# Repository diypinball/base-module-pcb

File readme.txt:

base-module-r1
==============
Size: Approx. 149mm x 99mm
Layers: 2
Silkscreen: White
Soldermask: Green
Thickness: 1.6mm

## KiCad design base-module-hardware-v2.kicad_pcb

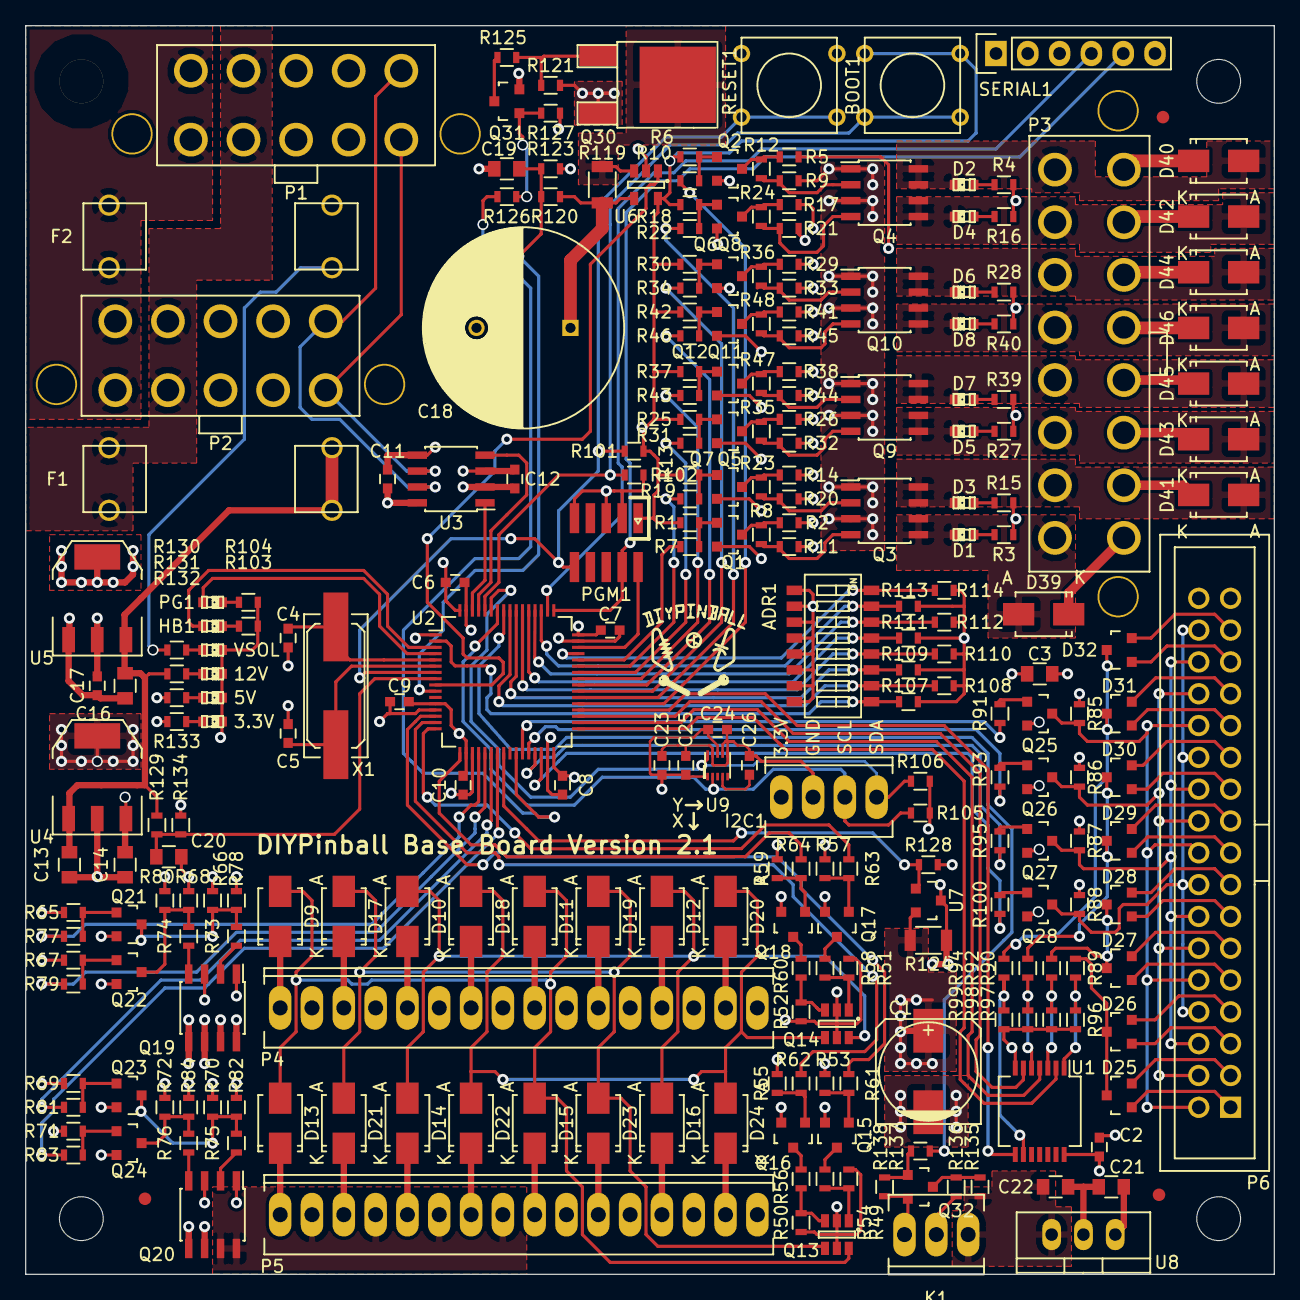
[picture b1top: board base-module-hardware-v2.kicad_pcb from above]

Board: 4 copper layers, 99.7 x 99.7 mm, 263 parts (0 on the bottom side), 197 nets.

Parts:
ADR1: DIPS_08; DIPSWITCH-SMT-08
BOOT1: BUTTON; SW_PUSH_SMALL
C1: 47u; c_elec_8x10
C2, C9, C10, C11, C12, C23, C24, C26: 100n; C_0603
C3, C13, C14, C16, C19, C20, C21, C22: 10u; C_0805
C4, C5: 18p; C_0603
C6, C7, C8: 10n; C_0603
C17: 4.7u; C_0603
C18: 470u; C_Radial_D16_L25_P7.5
C25: 1u; C_0603
D1, D2, D3, D4, D5, D6, D7, D8, D35, D36, D37, D38: LED; LED-0603
D9, D10, D11, D12, D13, D14, D15, D16, D17, D18, D19, D20, D21, D22, D23, D24, D39, D40, D41, D42, D43, D44, D45, D46: S1M; SMA_Standard
D25, D26, D27, D28, D29, D30, D31, D32: BAT54C; SOT-23
F1, F2: FUSE; FC203-20MM
FIDUCIAL: VAL**; FIDUCIAL
FIDUCIAL#2, FIDUCIAL#3: VAL**; FIDUCIAL
HB1: LED; LED-0603
I2C1: CONN_4; Socket_MOLEX-KK-RM2-54mm_Lock_4pin_straight
K1: CONN_3; Socket_MOLEX-KK-RM2-54mm_Lock_3pin_straight
P1, P2: PINBALL-CONNECTOR; PINBALL-CONNECTOR-V
P3: SOLENOID-CONNECTOR; SOLENOID-CONNECTOR-V
P4, P5: CONN_16; Socket_MOLEX-KK-RM2-54mm_Lock_16pin_straight
P6: HE10-34; BOXHEADER-0.100-34
PG1: LED; LED-0603
PGM1: ARM-SWD-HEADER; pin_array_5x2_50mil_smd
Q1, Q2, Q5, Q6, Q7, Q8, Q11, Q12, Q15, Q16, Q17, Q18, Q21, Q22, Q23, Q24, Q25, Q26, Q27, Q28, Q31: BC846; SOT-23
Q3, Q4, Q9, Q10, Q19, Q20: DMN6040SSD; SOIC-8_3.9x4.9mm_Pitch1.27mm
Q13, Q14: DMP2240UDM; SOT-23-6
Q30: FDD5614P; DPAK-2
Q32: BSS138; SOT-23
R1, R6, R8, R9, R13, R18, R20, R21, R25, R30, R32, R33, R37, R42, R44, R45, R49, R50, R51, R52, R53, R55, R57, R59, R65, R67, R69, R71, R78, R80, R82, R84, R85, R86, R87, R88, R89, R90, R92, R94, R96, R97, R98, R99, R101, R102, R107, R108, R109, R110, R111, R112, R113, R114, R121, R127, R138: 10K; R_0603
R2, R5, R7, R10, R14, R17, R19, R22, R26, R29, R31, R34, R38, R41, R43, R46, R54, R56, R58, R60, R61, R62, R63, R64, R66, R68, R70, R72, R77, R79, R81, R83, R91, R93, R95, R100, R103, R104, R126, R132, R133, R135: 1K; R_0603
R3, R4, R15, R16, R27, R28, R39, R40, R131: 2.7K; R_0603
R11, R12, R23, R24, R35, R36, R47, R48, R73, R74, R75, R76, R136, R137: 22; R_0603
R105, R106: 4.7K; R_0603
R119: .003; R_1206
R120: 95.3K 1%; R_0603
R123, R128, R134: 5.1K 1%; R_0603
R124: 0.075; R_1206
R125, R130: 27K; R_0603
R129: 20.5K 1%; R_0603
RESET1: BUTTON; SW_PUSH_SMALL
SERIAL1: FTDI_SERIAL; Socket_Strip_Straight_1x06
U1: 74LVC14; SSOP-14_5.3x6.2mm_Pitch0.65mm
U2: STM32F072R; LQFP-64_10x10mm_Pitch0.5mm
U3: MCP2562; SOIC-8_3.9x4.9mm_Pitch1.27mm
U4: MC78L05; SOT-223
U5: AP1117IE33G; SOT-223
U6: ZXCT1086E5TA; SOT-23-5
U7: ZXCT1107SA-7; SOT-23
U8: LM7805CT; TO-220_Neutral123_Vertical
U9: MMA8653FC; DFN-10
X1: 8.000 MHz; Q_49U3HMS

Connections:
+3.3V: ADR1.1, ADR1.2, ADR1.3, ADR1.4, ADR1.5, ADR1.6, ADR1.7, ADR1.8, BOOT1.2, C2.1, C6.1, C7.1, C8.1, C9.1, C10.1, C11.1, C17.1, C23.1, C24.1, C25.1, I2C1.1, PGM1.1, R1.1, R6.1, R13.1, R18.1, R25.1, R30.1, R37.1, R42.1, R65.1, R67.1, R69.1, R71.1, R101.1, R105.1, R106.1, R133.1, U1.14, U2.1, U2.13, U2.19, U2.32, U2.48, U2.64, U3.5, U5.2, U5.4, U6.5, U9.1, U9.8
+5V: C12.1, C14.1, R132.1, U3.3, U4.3
+12V: C3.1, C13.1, C16.1, C21.1, F1.2, P6.34, R2.1, R3.1, R4.1, R5.1, R14.1, R15.1, R16.1, R17.1, R26.1, R27.1, R28.1, R29.1, R38.1, R39.1, R40.1, R41.1, R85.1, R86.1, R87.1, R88.1, R124.2, R129.2, R131.1, U4.1, U5.3, U7.3, U8.1
/Accelerometer/SCL: I2C1.3, R105.2, U2.58, U9.2
/Accelerometer/SDA: I2C1.4, R106.2, U2.59, U9.10
/Control Logic/12V_SENSE: C20.1, R129.1, R134.1, U2.8
/Control Logic/ADDRESS0: ADR1.16, R114.1, U2.45
/Control Logic/ADDRESS1: ADR1.15, R113.1, U2.51
/Control Logic/ADDRESS2: ADR1.14, R112.1, U2.52
/Control Logic/ADDRESS3: ADR1.13, R111.1, U2.53
/Control Logic/ADDRESS4: ADR1.12, R110.1, U2.54
/Control Logic/ADDRESS5: ADR1.11, R109.1, U2.55
/Control Logic/ADDRESS6: ADR1.10, R108.1, U2.56
/Control Logic/ADDRESS7: ADR1.9, R107.1, U2.2
/Control Logic/BOOTLOADER: BOOT1.1, R102.1, U2.60
/Control Logic/CANH: P1.5, P2.5, U3.7
/Control Logic/CANL: P1.10, P2.10, U3.6
/Control Logic/CANRX: U2.61, U3.4
/Control Logic/CANTX: U2.62, U3.1
/Control Logic/HEARTBEAT: HB1.2, U2.3
/Control Logic/LAMP_COL0: R77.1, U2.20
/Control Logic/LAMP_COL1: R79.1, U2.21
/Control Logic/LAMP_COL2: R81.1, U2.22
/Control Logic/LAMP_COL3: R83.1, U2.23
/Control Logic/LAMP_ROW0: R61.1, U2.14
/Control Logic/LAMP_ROW1: R62.1, U2.15
/Control Logic/LAMP_ROW2: R63.1, U2.16
/Control Logic/LAMP_ROW3: R64.1, U2.17
/Control Logic/POWER_GOOD: PG1.2, U2.4
/Control Logic/RXD: SERIAL1.4, U2.50
/Control Logic/SOLENOID0: R7.1, U2.44
/Control Logic/SOLENOID1: R19.1, U2.43
/Control Logic/SOLENOID2: R31.1, U2.42
/Control Logic/SOLENOID3: R43.1, U2.41
/Control Logic/SOLENOID4: R46.1, U2.40
/Control Logic/SOLENOID5: R34.1, U2.39
/Control Logic/SOLENOID6: R22.1, U2.38
/Control Logic/SOLENOID7: R10.1, U2.37
/Control Logic/SWCLK: PGM1.4, SERIAL1.5, U2.49
/Control Logic/SWDIO: PGM1.2, U2.46
/Control Logic/VSOL_PRECHARGE_PWM: R126.2, U2.26
/Control Logic/VSOL_SENSE: C19.1, R120.2, R123.1, U2.10
/Control Logic/~RESET: PGM1.10, R101.2, RESET1.2, U2.7
/Lamp Driver/LAMP_12V: C1.1, Q13.2, Q13.5, Q14.2, Q14.5, R49.1, R50.1, R51.1, R52.1, R66.1, R68.1, R70.1, R72.1, R124.1, U7.2
/Power Supply/12V_IN: F1.1, P1.2, P1.7, P2.2, P2.7
/Power Supply/ILAMP_SENSE_OUT: R128.1, U2.24, U7.1
/Power Supply/ISOL_SENSE_OUT: U2.9, U6.1
/Power Supply/VSOL_IN: F2.1, P1.1, P1.6, P2.1, P2.6
/RGB LED Output/RGB_DATA: R137.2, U2.57
/Solenoid Driver/SOL_PWR: C18.1, D39.1, D40.1, D41.1, D42.1, D43.1, D44.1, D45.1, D46.1, P3.9, P3.10, P3.11, P3.12, P3.13, P3.14, P3.15, P3.16, R119.1, R120.1, U6.4
/Switch Matrix/COL0: R91.2, U2.27
/Switch Matrix/COL0_SWITCHED: P6.2, P6.10, P6.18, P6.26, Q25.3, R85.2
/Switch Matrix/COL1: R93.2, U2.28
/Switch Matrix/COL1_SWITCHED: P6.4, P6.12, P6.20, P6.28, Q26.3, R86.2
/Switch Matrix/COL2: R95.2, U2.29
/Switch Matrix/COL2_SWITCHED: P6.6, P6.14, P6.22, P6.30, Q27.3, R87.2
/Switch Matrix/COL3: R100.2, U2.30
/Switch Matrix/COL3_SWITCHED: P6.8, P6.16, P6.24, P6.32, Q28.3, R88.2
/Switch Matrix/ROW0: U1.2, U2.33
/Switch Matrix/ROW0_SWITCHED: D25.3, D26.3, R89.2
/Switch Matrix/ROW1: U1.4, U2.34
/Switch Matrix/ROW1_SWITCHED: D27.3, D28.3, R90.2
/Switch Matrix/ROW2: U1.6, U2.35
/Switch Matrix/ROW2_SWITCHED: D29.3, D30.3, R92.2
/Switch Matrix/ROW3: U1.8, U2.36
/Switch Matrix/ROW3_SWITCHED: D31.3, D32.3, R94.2
GND: C1.2, C2.2, C3.2, C4.2, C5.2, C6.2, C7.2, C8.2, C9.2, C10.2, C11.2, C12.2, C13.2, C14.2, C16.2, C17.2, C18.2, C19.2, C20.2, C21.2, C22.2, C23.2, C24.2, C25.2, C26.2, D35.1, D36.1, D37.1, D38.1, I2C1.2, K1.3, P1.3, P1.4, P1.8, P1.9, P2.3, P2.4, P2.8, P2.9, P6.33, PGM1.3, PGM1.5, PGM1.9, Q1.2, Q2.2, Q3.1, Q3.3, Q4.1, Q4.3, Q5.2, Q6.2, Q7.2, Q8.2, Q9.1, Q9.3, Q10.1, Q10.3, Q11.2, Q12.2, Q15.2, Q16.2, Q17.2, Q18.2, Q19.1, Q19.3, Q20.1, Q20.3, Q21.2, Q22.2, Q23.2, Q24.2, Q25.2, Q26.2, Q27.2, Q28.2, Q31.2, Q32.2, R8.1, R9.1, R20.1, R21.1, R32.1, R33.1, R44.1, R45.1, R53.1, R55.1, R57.1, R59.1, R78.2, R80.2, R82.2, R84.2, R96.2, R97.2, R98.2, R99.2, R102.2, R103.2, R104.2, R107.2, R108.2, R109.2, R110.2, R111.2, R112.2, R113.2, R114.2, R123.2, R127.2, R128.2, R134.2, R138.2, RESET1.1, SERIAL1.1, U1.7, U2.12, U2.18, U2.31, U2.47, U2.63, U3.2, U3.8, U4.2, U4.4, U5.1, U6.2, U8.2, U9.6, U9.7, U9.9
unnamed: C4.1, U2.5, X1.1
unnamed: C5.1, U2.6, X1.2
unnamed: C22.1, K1.1, R135.1, U8.3
unnamed: C26.1, U9.4
unnamed: D1.1, D39.2, P3.1, Q3.5, Q3.6
unnamed: D1.2, R3.2
unnamed: D2.1, D40.2, P3.8, Q4.7, Q4.8
unnamed: D2.2, R4.2
unnamed: D3.1, D41.2, P3.2, Q3.7, Q3.8
unnamed: D3.2, R15.2
unnamed: D4.1, D42.2, P3.7, Q4.5, Q4.6
unnamed: D4.2, R16.2
unnamed: D5.2, R27.2
unnamed: D6.2, R28.2
unnamed: D7.2, R39.2
unnamed: D8.2, R40.2
unnamed: D9.1, P4.1
unnamed: D10.1, P4.5
unnamed: D10.2, D12.2, D14.2, D16.2, Q14.6
unnamed: D11.1, P4.9
unnamed: D9.2, D11.2, D13.2, D15.2, Q13.6
unnamed: D12.1, P4.13
unnamed: D13.1, P5.1
unnamed: D14.1, P5.5
unnamed: D15.1, P5.9
unnamed: D16.1, P5.13
unnamed: D17.1, P4.3
unnamed: D17.2, D19.2, D21.2, D23.2, Q13.4
unnamed: D18.1, P4.7
unnamed: D18.2, D20.2, D22.2, D24.2, Q14.4
unnamed: D19.1, P4.11
unnamed: D20.1, P4.15
unnamed: D21.1, P5.3
unnamed: D22.1, P5.7
unnamed: D23.1, P5.11
unnamed: D24.1, P5.15
unnamed: D25.1, P6.1
unnamed: D25.2, P6.3
unnamed: D26.1, P6.5
unnamed: D26.2, P6.7
unnamed: D27.1, P6.9
unnamed: D27.2, P6.11
unnamed: D28.1, P6.13
unnamed: D28.2, P6.15
unnamed: D29.1, P6.17
unnamed: D29.2, P6.19
unnamed: D30.1, P6.21
unnamed: D30.2, P6.23
unnamed: D31.1, P6.25
unnamed: D31.2, P6.27
unnamed: D32.1, P6.29
unnamed: D32.2, P6.31
unnamed: D35.2, R130.2
unnamed: D36.2, R131.2
unnamed: D37.2, R132.2
unnamed: D38.2, R133.2
unnamed: D5.1, D43.2, P3.3, Q9.5, Q9.6
unnamed: D6.1, D44.2, P3.6, Q10.7, Q10.8
unnamed: D7.1, D45.2, P3.4, Q9.7, Q9.8
unnamed: D8.1, D46.2, P3.5, Q10.5, Q10.6
unnamed: HB1.1, R103.1
unnamed: K1.2, R136.1
unnamed: P4.2, P4.4, P4.6, P4.8, Q19.7, Q19.8
unnamed: P4.10, P4.12, P4.14, P4.16, Q19.5, Q19.6
unnamed: P5.2, P5.4, P5.6, P5.8, Q20.7, Q20.8
unnamed: P5.10, P5.12, P5.14, P5.16, Q20.5, Q20.6
unnamed: PG1.1, R104.1
unnamed: Q1.1, R1.2, R7.2
unnamed: Q1.3, R2.2, R11.2
unnamed: Q2.1, R6.2, R10.2
unnamed: Q2.3, R5.2, R12.1
unnamed: Q3.2, R20.2, R23.1
unnamed: Q3.4, R8.2, R11.1
unnamed: Q4.2, R9.2, R12.2
unnamed: Q4.4, R21.2, R24.2
unnamed: Q5.1, R13.2, R19.2
unnamed: Q5.3, R14.2, R23.2
unnamed: Q6.1, R18.2, R22.2
unnamed: Q6.3, R17.2, R24.1
unnamed: Q7.1, R25.2, R31.2
unnamed: Q7.3, R26.2, R35.2
unnamed: Q8.1, R30.2, R34.2
unnamed: Q8.3, R29.2, R36.1
unnamed: Q9.2, R44.2, R47.1
unnamed: Q9.4, R32.2, R35.1
unnamed: Q10.2, R33.2, R36.2
unnamed: Q10.4, R45.2, R48.2
unnamed: Q11.1, R37.2, R43.2
unnamed: Q11.3, R38.2, R47.2
unnamed: Q12.1, R42.2, R46.2
unnamed: Q12.3, R41.2, R48.1
unnamed: Q13.1, R49.2, R54.1
unnamed: Q13.3, R50.2, R56.1
unnamed: Q14.1, R51.2, R58.1
unnamed: Q14.3, R52.2, R60.1
unnamed: Q15.1, R53.2, R61.2
unnamed: Q15.3, R54.2
unnamed: Q16.1, R55.2, R62.2
unnamed: Q16.3, R56.2
unnamed: Q17.1, R57.2, R63.2
unnamed: Q17.3, R58.2
unnamed: Q18.1, R59.2, R64.2
unnamed: Q18.3, R60.2
unnamed: Q19.2, R73.1
unnamed: Q19.4, R74.2
unnamed: Q20.2, R75.2
unnamed: Q20.4, R76.2
unnamed: Q21.1, R65.2, R77.2
unnamed: Q21.3, R66.2, R73.2, R78.1
unnamed: Q22.1, R67.2, R79.2
unnamed: Q22.3, R68.2, R74.1, R80.1
unnamed: Q23.1, R69.2, R81.2
unnamed: Q23.3, R70.2, R75.1, R82.1
unnamed: Q24.1, R71.2, R83.2
unnamed: Q24.3, R72.2, R76.1, R84.1
unnamed: Q25.1, R91.1
unnamed: Q26.1, R93.1
unnamed: Q27.1, R95.1
unnamed: Q28.1, R100.1
unnamed: Q30.D, R119.2, U6.3
unnamed: Q30.G, R121.2, R125.1
unnamed: Q31.1, R126.1, R127.1
unnamed: Q31.3, R125.2
unnamed: Q32.1, R137.1, R138.1
unnamed: Q32.3, R135.2, R136.2
unnamed: R89.1, R96.1, U1.1
unnamed: R90.1, R97.1, U1.3
unnamed: R92.1, R98.1, U1.5
unnamed: R94.1, R99.1, U1.9
VEE: F2.2, Q30.S, R121.1, R130.1

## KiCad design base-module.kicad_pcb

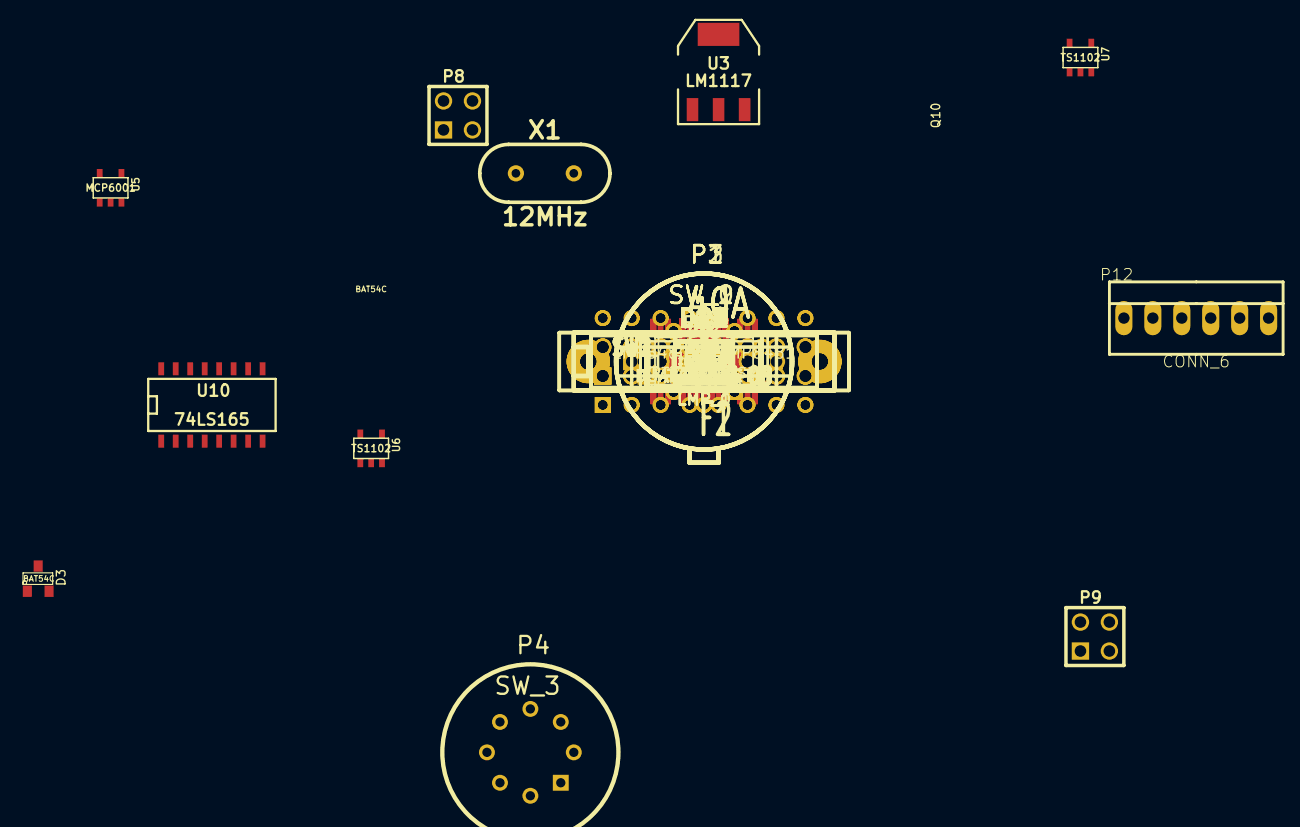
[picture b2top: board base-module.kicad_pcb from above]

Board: 2 copper layers, 203 parts (0 on the bottom side), 137 nets, no tracks yet.

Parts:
3V1, 5V1, 12V1: LED; LED-0805
C1, C2, C3, C4: CYA; SM0805
C5: 100n; SM0805
C6: 10uF; SM1206POL
C7, C8, C10, C14, C15, C20: 100nF; SM0805
C9: 3.3nF; SM0805
C11: DNP; SM0805
C12: 22uF; SM0805
C13: 22nF; SM0805
C16, C17: 0.047uF; SM0805
C18, C27: 100nf; SM0805
C19, C22, C23, C26: C; SM0805
C21, C25: 10nF; SM0805
C24: 1nF; SM0805
D1, D2, D3, D4, D5, D6, D7, D8: BAT54C; SOT23
D9, D10, D11, D12: ZENERSMALL; SOT23
D13, D14, D17, D18, D21, D22, D25, D26: DIODE; Diode-SMA_Handsoldering_RevA_27July2010
D15, D16, D19, D20, D23, D24, D27, D28: LED; LED-0805
D29: DNP; Diode-SMA_Handsoldering_RevA_27July2010
D30, D31: ZENER; SOT23
DBG1: LED; LED-0805
F1, F2: 40A; FUSE5-20
HB1: LED; LED-0805
L1: 15uH; SM2512
P1: SW_0; H08
P2: SW_2; H08
P3: SW_1; H08
P4: SW_3; H08
P5: LMP_0; pin_array_8x2
P6: LMP_1; pin_array_8x2
P7, P8, P9, P10: CONN_2X2; PIN_ARRAY_2X2
P11: CONN_5; PIN_ARRAY-6X1
P12: CONN_6; PINHEAD1-6
P13: CONN_4; PIN_ARRAY_4x1
P14: JTAG; PIN_ARRAY_5x2
PWR1: LED; LED-0805
Q1, Q2, Q3, Q4, Q5, Q6, Q7, Q8, Q9, Q10, Q11, Q12, Q17, Q18, Q19, Q20, Q21, Q22, Q23, Q24: NPN; SOT23
Q13, Q15: DUAL_MOSFET_P; SO8N
Q14, Q16, Q25, Q26, Q27, Q28: DUAL_MOSFET_N; SO8N
R1, R2, R3, R4, R5, R6, R7, R8, R9, R10, R11, R12, R13, R14, R15, R16, R17, R18, R19, R20, R21, R22, R23, R24, R25, R26, R27, R28, R29, R30, R31, R32, R33, R34, R35, R36, R37, R38, R39, R40, R41, R42, R43, R44, R49, R52, R53, R54, R55, R60, R61, R62, R63, R64, R65, R66: R; SM0805
R45: 100k; SM0805
R46: 20k; SM0805
R47: 62k; SM0805
R48: 11.8k; SM0805
R50: 680; SM0805
R51: 1K; SM0805
R56: 0; SM0805
R57: DNP; SM0805
R58, R59: 60; SM0805
RP1, RP2, RP3, RP4, RP5, RP6, RP7, RP8, RP9, RP10, RP11, RP12, RP13: R_PACK4; SM0805
RP14, RP15: R_PACK8; SM0805
SW1, SW2: DIPS_08; DIP-16__300
U1: 74HC14; SO14E
U2: RT7247AHGSP; SO8E
U3: LM1117; SOT223
U4: LMP8480_/_LMP8481; MSOP_8
U5: MCP6001; SOT23-5
U6, U7: TS1102; SOT23-5
U9: 74LS595; SO16N
U10, U11: 74LS165; SO16N
X1: 12MHz; HC-49V

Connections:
+3.3V: C5.1, C13.1, C18.1, C20.1, C21.1, C25.1, P13.1, R44.1, R57.1, R60.1, R63.1, R64.1, R65.1, SW1.1, SW1.2, SW1.3, SW1.4, SW1.5, SW1.6, SW1.7, SW1.8, SW2.1, SW2.2, SW2.3, SW2.4, SW2.5, SW2.6, SW2.7, SW2.8, U1.14, U3.2, U9.10, U9.16, U10.16, U11.16
+5V: C12.1, C14.1, C15.1, C27.1, D29.1, L1.2, R43.1, R47.1, U3.3, U4.2, U5.5
+12V: C6.1, F2.2, R42.1, R45.1, R52.1, R53.1, R61.1, U2.2, U6.5, U7.5
/3V3CurrentSense/SENSE_OUT: C16.1, U6.3
/Controller/12V_SENSE_VOLTAGE: C26.1, D31.2, R61.2, R62.1
/Controller/CANH: P11.3, R58.1
/Controller/CANL: P11.4, R59.2
/Controller/DIP_CLOCK: U10.2, U11.2
/Controller/DIP_LOAD: U10.1, U11.1
/Controller/HB_LED: DBG1.2, R66.1
/Controller/I2C_C: P13.3, R64.2
/Controller/I2C_D: P13.4, R63.2
/Controller/JTAG_RESET: P14.10, R60.2
/Controller/LMP_CURRENT: C17.1, U7.3
/Controller/LMP_ROW_0: RP8.1, U9.15
/Controller/LMP_ROW_1: RP8.2, U9.1
/Controller/SOL_PWR_SENSE_VOLTAGE: C19.1, D30.2, R54.2, R55.1
/CurrentSense/PWR_OUT: D13.2, D14.2, D17.2, D18.2, D21.2, D22.2, D25.2, D26.2, P7.2, P7.4, P8.2, P8.4, P9.2, P9.4, P10.2, P10.4, R17.1, R19.1, R21.1, R23.1, R25.1, R27.1, R29.1, R31.1, R33.1, R34.1, R35.1, R36.1, R37.1, R38.1, R39.1, R40.1, R49.2, U4.8
/CurrentSense/SNS_OUT: R50.1, U5.1
/LampMatrix/COL0: RP7.1, RP9.1, U9.4
/LampMatrix/COL1: RP7.2, RP9.2, U9.5
/LampMatrix/LMP_0M: P5.2, P5.10, P6.2, P6.10
/LampMatrix/LMP_0P: P5.1, P5.3, P5.5, P5.7
/LampMatrix/LMP_1M: P5.4, P5.12, P6.4, P6.12
/LampMatrix/LMP_1P: P5.9, P5.11, P5.13, P5.15
/LampMatrix/LMP_2M: P5.6, P5.14, P6.6, P6.14
/LampMatrix/LMP_2P: P6.1, P6.3, P6.5, P6.7
/LampMatrix/LMP_3M: P5.8, P5.16, P6.8, P6.16
/LampMatrix/LMP_3P: P6.9, P6.11, P6.13, P6.15
/LampMatrix/LMP_PWR: R1.1, R3.1, R5.1, R7.1, R9.1, R11.1, R13.1, R15.1, R53.2, U7.4
/PowerSupply/12V: F2.1, P11.2
/PowerSupply/50V: F1.1, P11.1
/PowerSupply/Power_EN: C7.1, R45.2, U2.7
/SolenoidDriver/SOLENOID0: RP10.1, RP12.1
/SolenoidDriver/SOLENOID1: RP10.2, RP12.2
/SolenoidDriver/SOLENOID4: RP11.1, RP13.1
/SolenoidDriver/SOLENOID5: RP11.2, RP13.2
/SwitchMatrix/12V_IN: R52.2, RP1.1, RP1.2, U6.4
/SwitchMatrix/COL0: RP2.1, RP3.1
/SwitchMatrix/COL0_POWERED: P1.1, P2.1, P3.1, P4.1, Q1.3
/SwitchMatrix/COL1: RP2.2, RP3.2
/SwitchMatrix/COL1_POWERED: P1.3, P2.3, P3.3, P4.3, Q2.3
/SwitchMatrix/COL2_POWERED: P1.5, P2.5, P3.5, P4.5, Q3.3
/SwitchMatrix/COL3_POWERED: P1.7, P2.7, P3.7, P4.7, Q4.3
/SwitchMatrix/ROW0_MATRIX: D1.3, D2.3, RP5.1
/SwitchMatrix/ROW1_MATRIX: D5.3, D6.3, RP5.2
/SwitchMatrix/ROW2_MATRIX: D3.3, D4.3
/SwitchMatrix/ROW3_MATRIX: D7.3, D8.3
GND: 3V1.2, 5V1.2, 12V1.2, C1.2, C2.2, C3.2, C4.2, C5.2, C6.2, C7.2, C8.2, C11.2, C12.2, C13.2, C14.2, C15.2, C16.2, C17.2, C18.2, C19.2, C20.2, C21.2, C22.2, C23.2, C24.2, C25.2, C26.2, C27.2, D9.1, D10.1, D11.1, D12.1, D30.1, D31.1, HB1.2, P11.5, P12.1, P13.2, P14.3, P14.5, P14.9, PWR1.2, Q1.1, Q2.1, Q3.1, Q4.1, Q5.1, Q6.1, Q7.1, Q8.1, Q9.1, Q10.1, Q11.1, Q12.1, Q17.1, Q18.1, Q19.1, Q20.1, Q21.1, Q22.1, Q23.1, Q24.1, R2.2, R4.2, R6.2, R8.2, R10.2, R12.2, R14.2, R16.2, R18.2, R20.2, R22.2, R24.2, R26.2, R28.2, R30.2, R32.2, R46.2, R48.2, R51.2, R55.2, R56.1, R62.2, RP4.1, RP4.2, RP6.1, RP6.2, RP14.1, RP14.2, RP15.1, RP15.2, U1.7, U2.4, U3.1, U4.4, U5.2, U6.1, U6.2, U7.1, U7.2, U9.8, U9.13, U10.8, U10.10, U10.15, U11.8, U11.15
unnamed: D6.2, P3.8
unnamed: D6.1, P3.6
unnamed: D5.1, P3.4
unnamed: D5.2, P3.2
unnamed: D1.2, P1.2
unnamed: D2.2, P1.8
unnamed: D1.1, P1.4
unnamed: D2.1, P1.6
unnamed: D8.1, P4.6
unnamed: D8.2, P4.8
unnamed: D7.1, P4.4
unnamed: D7.2, P4.2
unnamed: D3.2, P2.2
unnamed: D3.1, P2.4
unnamed: D4.1, P2.6
unnamed: D4.2, P2.8
unnamed: C1.1, D9.3, U1.1
unnamed: C4.1, D12.3, U1.9
unnamed: C3.1, D11.3, U1.5
unnamed: C2.1, D10.3, U1.3
unnamed: Q11.3, R13.2, R14.1
unnamed: Q5.3, R1.2, R2.1
unnamed: Q9.3, R9.2, R10.1
unnamed: Q7.3, R5.2, R6.1
unnamed: Q6.3, R3.2, R4.1
unnamed: Q12.3, R15.2, R16.1
unnamed: Q10.3, R11.2, R12.1
unnamed: Q8.3, R7.2, R8.1
unnamed: D14.1, D16.2, P8.1
unnamed: Q20.3, R23.2, R24.1
unnamed: Q18.3, R19.2, R20.1
unnamed: Q24.3, R31.2, R32.1
unnamed: Q22.3, R27.2, R28.1
unnamed: D20.1, R36.2
unnamed: D24.1, R38.2
unnamed: D28.1, R40.2
unnamed: D26.1, D28.2, P10.3
unnamed: D22.1, D24.2, P10.1
unnamed: D18.1, D20.2, P8.3
unnamed: D16.1, R34.2
unnamed: D15.1, R33.2
unnamed: D19.1, R35.2
unnamed: D23.1, R37.2
unnamed: D27.1, R39.2
unnamed: D25.1, D27.2, P9.3
unnamed: D21.1, D23.2, P9.1
unnamed: D17.1, D19.2, P7.3
unnamed: D13.1, D15.2, P7.1
unnamed: Q19.3, R21.2, R22.1
unnamed: Q21.3, R25.2, R26.1
unnamed: Q17.3, R17.2, R18.1
unnamed: Q23.3, R29.2, R30.1
unnamed: C10.1, D29.2, U2.1
unnamed: 5V1.1, R43.2
unnamed: 3V1.1, R44.2
unnamed: PWR1.1, R41.2
unnamed: 12V1.1, R42.2
unnamed: R47.2, R48.1, U2.5
unnamed: C8.1, U2.8
unnamed: C10.2, L1.1, U2.3
unnamed: C9.2, R46.1
unnamed: C9.1, C11.1, U2.6
unnamed: DBG1.1, R65.2
unnamed: SW1.11, U10.4
unnamed: SW1.9, U10.6
unnamed: SW1.10, U10.5
unnamed: SW1.12, U10.3
unnamed: SW2.13, U11.14
unnamed: SW2.14, U11.13
unnamed: SW1.16, U10.11
unnamed: SW1.15, U10.12
unnamed: SW1.14, U10.13
unnamed: SW1.13, U10.14
unnamed: SW2.12, U11.3
unnamed: SW2.11, U11.4
unnamed: SW2.10, U11.5
unnamed: SW2.9, U11.6
unnamed: U10.9, U11.10
unnamed: SW2.16, U11.11
unnamed: SW2.15, U11.12
unnamed: C24.1, R58.2, R59.1
unnamed: R56.2, R57.2
unnamed: HB1.1, R66.2
unnamed: C23.1, X1.1
unnamed: C22.1, X1.2
unnamed: R50.2, R51.1, U5.4
unnamed: U4.5, U5.3
SOL_PWR_F: F1.2, R41.1, R49.1, R54.1, U4.1

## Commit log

2013-04-09 Adding structure of new schematic project
2013-04-09 Adding hierarchy of schematics to project
2013-04-10 Started work on switch matrix.
2013-04-10 Added library for custom parts Switch matrix and solenoid driver mostly done
2013-04-10 Updating switch matrix to use pullups on row inputs rather than pulldowns, so that it will actually work
2013-04-13 Fixed switch matrix to match Mike's sketches Added lamp matrix
2013-04-14 Added the mcu and testing the git commit
2013-04-14 Changed the controller symbol for the LPC11C24 added some of the support components,played with the larger blocks
2013-04-14 changed the voltage lbaels to global labels
2013-04-15 did the power sheet
2013-04-15 updated the power circut to include the more hidden preferences on the data sheet
2013-04-15 added some stuff to the main controller schematic
2013-04-16 power updated still need to add underpad also changed input connector to 5 pin and added fuses, added current sense with op-amp for solinoids
2013-04-16 added the other two current sense outputs and modified the power circut, i cant seem to add the 9th pad, the bottom thermal pad????
2013-04-17 added dip switch library and modifed current sense's to add capsstarted the main controller page
2013-04-17 changed the controller adding some shift registers
2013-04-18 finished main controller, added LED's to power system.
2013-04-18 ran an ERC and touched up a couple small issues
2013-04-19 added some more info to the different components, changed the pinout for zeeners, and am hating ki-cad for schematic to pads.
2013-04-27 added more footprints, connectors and inductors are currently wronggit add .git add . must be changed
2013-04-29 Editing .gitignore to include EAGLE temp files as well now
2013-04-29 Adding EAGLE version of schematic. Needs some cleaning, almost done.
2013-04-30 Finished schematic, and renamed. Added start of board file, with some layout done.
2013-04-30 Switched solenoid connectors to 2 2x4 instead of 4 2x2
2013-05-02 More routing work
2013-05-07 added another file with suffex MI for some testing of other layout methods
2013-05-09 wtf is happening
2013-05-10 More layout work. Changed connections to lamp matrix to make the layout easier. Started adding planes. Trying to go for a ground-only fill on the bottom layer.
2013-05-11 More layout work done. So far the board is fitting in 10cm x 15cm, but MUCH more routing is to be done.
2013-05-12 All parts placed, everything but power and CAN looks to be routed. Hoping someone can pick up where I left off - I'm done for now.
2013-05-13 changed via locations to reduce drc errors, and routed CAN lines
2013-05-14 no more ratsnets and good drc
2013-05-15 added full ground plane over top layer, changed silkscreen
2013-05-17 Cleaned up silkscreen and made ground plane continuous. Then cut out ground plane around middle digital section somewhat to keep switching noise from transistors from interfering with microcontroller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
2013-05-17 Removing old KiCAD stuff
2013-05-20 Added some capacitance to the supply rails, 12V and 50V. Might be a good idea, what with all the instantaneous current draw and what not.
2013-05-20 Added some more part numbers. All we need to do at this point is verify the shunt resistors for the current sensing, and I think we're good to go.
2013-05-29 Adding Gerbers and logos to board. Removing MI version of board, as we're not using it. BOARDS ORDERED.
2013-06-02 modified resistor values, changd the n-fet for the lamps to bo inline with the solinoid controller.
2013-09-16 Adding version 1.1 of the hardware, fixing a few bugs
2014-03-17 Adding start of version 2.0 hardware, using KiCAD
2014-03-17 Added RGB output and finished power supply monitor schematic, including new current monitor and voltage monitor divider values.
2014-04-02 Adding I2C connector and reannotating to reflect that
2015-02-22 Cleaning up schematic Updating solenoid driver to use 12V for MOSFET gates instead of Vsol so we never exceed Vgs_max
2015-06-01 Started layout on 2.0
2015-06-01 Tweaking layout to make power supply fit
2015-06-03 Everything fits on the board area now. Still need to finish wiring.
2015-06-04 2.0 is getting very close. Adjusted the solenoid connections to allow a cleaner layout.
2015-06-04 Power layers set up. A few footprint/pinout changes and some silkscreen cleanup, and the first rev is complete.
2015-06-04 100% routed.
2015-06-05 Finished layout! Needs review.
2015-06-07 Added OSHW logo
2015-06-15 Fixing BAT54C pinout, and some feedback from layout review.
2015-06-15 Updated solenoid driver with new resistor arrangement, and changed footprint on switch matrix to a connector we can actually get.
2015-06-26 Finishing layout updates from review with Mike.
2015-06-26 Logo placement adjustment
2015-06-26 Adding CAM data
2015-06-28 Fixed labelling of axes on accelerometer.
2015-10-16 Removing old version
2015-10-16 Committing latest files. This includes the KiCAD 4.0.0rc1 migration as well as the updates to Base Board 2.1.
2015-10-16 Moving 2.x files to root
2015-10-25 Fixing reversed 5V regulator and adding polarized header for WS2812B strip output.
2016-09-09 Latest changes (so old I don't remember)
